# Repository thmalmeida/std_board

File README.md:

# std_board
_std_board_ is an open hardware project that aims to bring the connectivity capacity of a microcontroller joining with sensors and actuators to a remote monitoring and control.

Renderized PCB with electrical components and modules are showed on the following picture.

# update logs

- 20210901
  + Voltage divider resistor values has been calculated sucessfully;
  + AC voltage measure sensor simulation has updated for 127 and 220 Vrms;
  + 

- 20210719
 - Fix voltage measure circuit on R58;
 - Modify voltage measure input borne to left side board avoid AC DC short circuits

# Content

* [About std_board](#about-std_board)
* [Features](#features)
* [Peripherals mapping](#peripherals-mapping)
* [Digital inputs](#digitadigitall-inputs)
* [Level sensor](#level-sensor)
* [Voltage sensor](#voltage-sensor)
* [Power input modes](#power_input_modes)
  + [Mode 1: 120-240 VAC input](#mode-1-120-240-vac-input)
  + [Mode 2: 24 VAC input](#mode-2-24-vac-input)
  + [Mode 3: 5 Vdc (external power supply)](#mode-3-5V)
* [Current controller](#current-controller)
* [AC load drive](#ac-load-drive)
* [Erros fixed on v0.1.0](#erros)

## About std_board

The main idea of std_board is help farmers to optimize production and monitoring some variables. Even this hardware is a little bit generic pplication that can control water pumps, valves, solenoids and any AC load. For this, it needs some feedback o real world physical variables like water weel level, time, water pressure inside pumps, ac voltage, ac current, thermal relay, and any digital input. The general purpose is optimize the production controlling the water flux.

The main concept of this system is interfaces one processor, e.g. ESP32, with electrical AC loads and physical parameters.

## Peripherals mapping

Pin map table of ESP32 onboard connections
.

The onboard system has the following connectivities:

## Features
This board has few hardware printed circuits that interfaces the ESP32 with real world variables conditioning physical variables to low voltages signals readable for input micro controller.

* Digital I/O (four)
* Input for pressure sensor;
* Input for temperature one wire temperature sensor (e.g. DS18B20);
* Umidity sensor DHT11;
* Current controller using internal DAC and onboard circuit processing;
* Protection circuit;
* AC voltage sensor;
* AC current sensor;
* AC load drive;
* JTAG connector - for debbugger (e.g. FT2232H);
* I2C connection for RTC module (e.g. DS3231);
* I2C connection for barometric sensor (e.g. BMP280);
* Four independent water level sensor circuits;
* Onboard LED indicator;
* Power supply with capability with different voltage levels input;

### Digital I/O

Four digital I/O are mounted with 56 kOhms pull up resistors and low pass filter using 47 nF capactitor. The circuit are showing on the following Figure.

### Level sensor

This board has four independent water level sensor circuit. Each circuit uses one BJT (bipolar junction transistor) and has one jump to exclude this transistor if desired. The main concept of this circuit a voltage division with amplification. The transistor has the function to amplifier the signal and transform it in a digital.

Some simulation has been done

## Voltage sensor
The voltage sensor can measure four different source of voltages into one selected soldering jump. The following Figure shows the schematic of voltage sensor circuit.

## Power input modes

### Mode 1: 120-240 VAC input
This mode
to 12VDC and 120 mA;
### Mode 2: 24 VAC to 5 VDC;
20211012 - This mode should be defined, calculated e design in a future moment. Linear regulation has a big waste on drop difference voltage when the input is ~40 V. Bests solutions were found using switching regulators. LNK30x series has bigger input AC voltage. Some candidates with low voltages are:

- LM2576
- LM2596
- DPA422GN
- XL7015

Switches regulators has best efficiency when drop difference voltage are considerable.

### Mode 3: 5 Vdc (external power supply)

If the system is powered with external 5 V power supply on Pwr_in_1 (0V) and Pwr_in_2 (+5V), it needs to solder some following jumps:

- J31: to jump F3 fuse;
- J32: to jump L1 protection inductor;
- J33 and J43: to jump rectifer 1;
- J40: to jump L2 filter;
- J41: link node A with node B;
- J44: link node B to node C;
- J42: jump 5 V regulation because it's powered directly with external 5 V;
- J35: to link the 5 V with whole system;

## Current controller

## AC load drive

This boards has three circuits to drive AC voltage from source to the load using TRIAC and optocoupler components. Some filters to avoid unexpected shots are implemented on the power side. The Figure bellow shows the drive where one high logic digital signal from +3,3 V to +5 V can be applied on <em>K1_out</em> point and shotting the TRIAC. The <em>Power_AC_2</em> is the main phase that drives throug the TRIAC to de <em>Load1</em> node. This load must be connected to another phase or to neutro to make a close circuit.

It needs to put a F1 fuse or solder J36 jump.

# Setup #1 on 0.1.0 version (20210310):

This part guide to build one setup to common use. The nexts steps should be followed to connect jumps to link electrical parts.

- J9: connect the common pad wire to 3.3V on water level circuits;
- R73: can be short circuited
- J27: exclude the first pad and connect T1 input to fifth pad;
- J16: substitute abstract diode D4 protection;
- J25: solder jump to connect L3 water level using GPIO14;
- J26: solder jump to connect L2 water level using GPIO12;
- J19: connect umidity sensor on GPIO13;

- Current source drive circuit
Should solder J24 to use ADC read on GPIO26 into ADC2_9;

## Hardware mounted onboard

* Pressure circuit bias 1;
* Pressure circuit bias 2;

# Setup #2

# Setup #3

# Tips
To use L1 and L4 circuit level sensor should solder the following jumps:

L1: put jump J22 closed;
L4: put jump J7 closed;

# Errors

- Voltage sensor

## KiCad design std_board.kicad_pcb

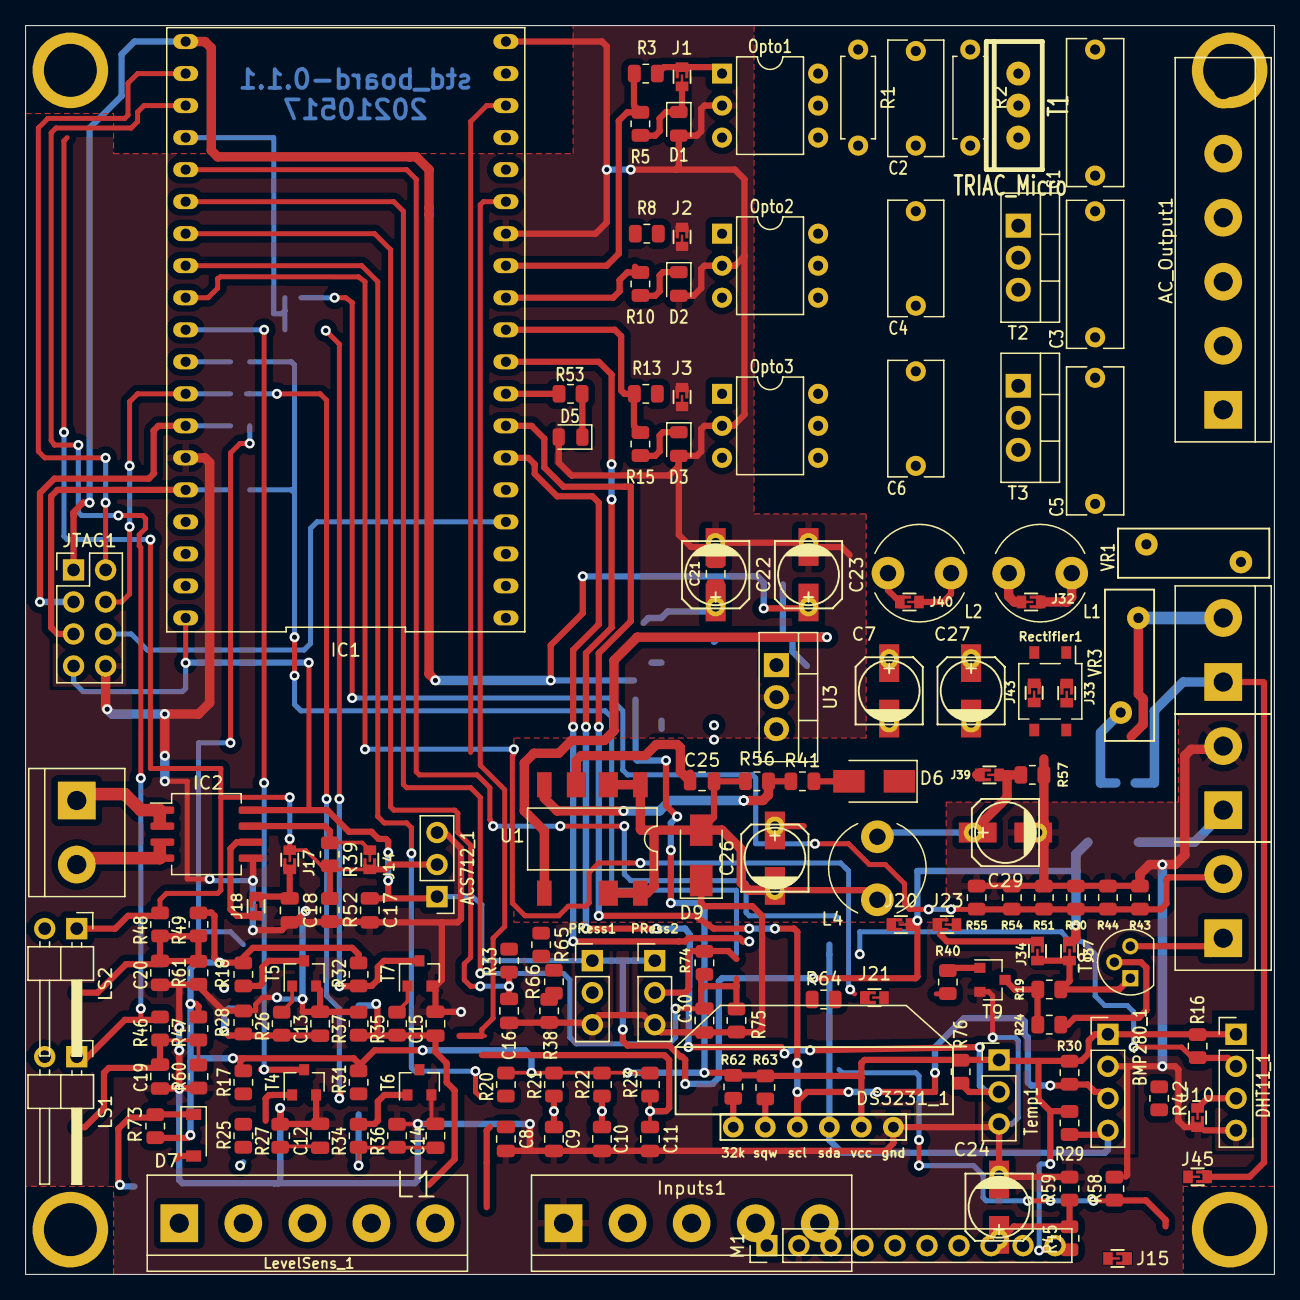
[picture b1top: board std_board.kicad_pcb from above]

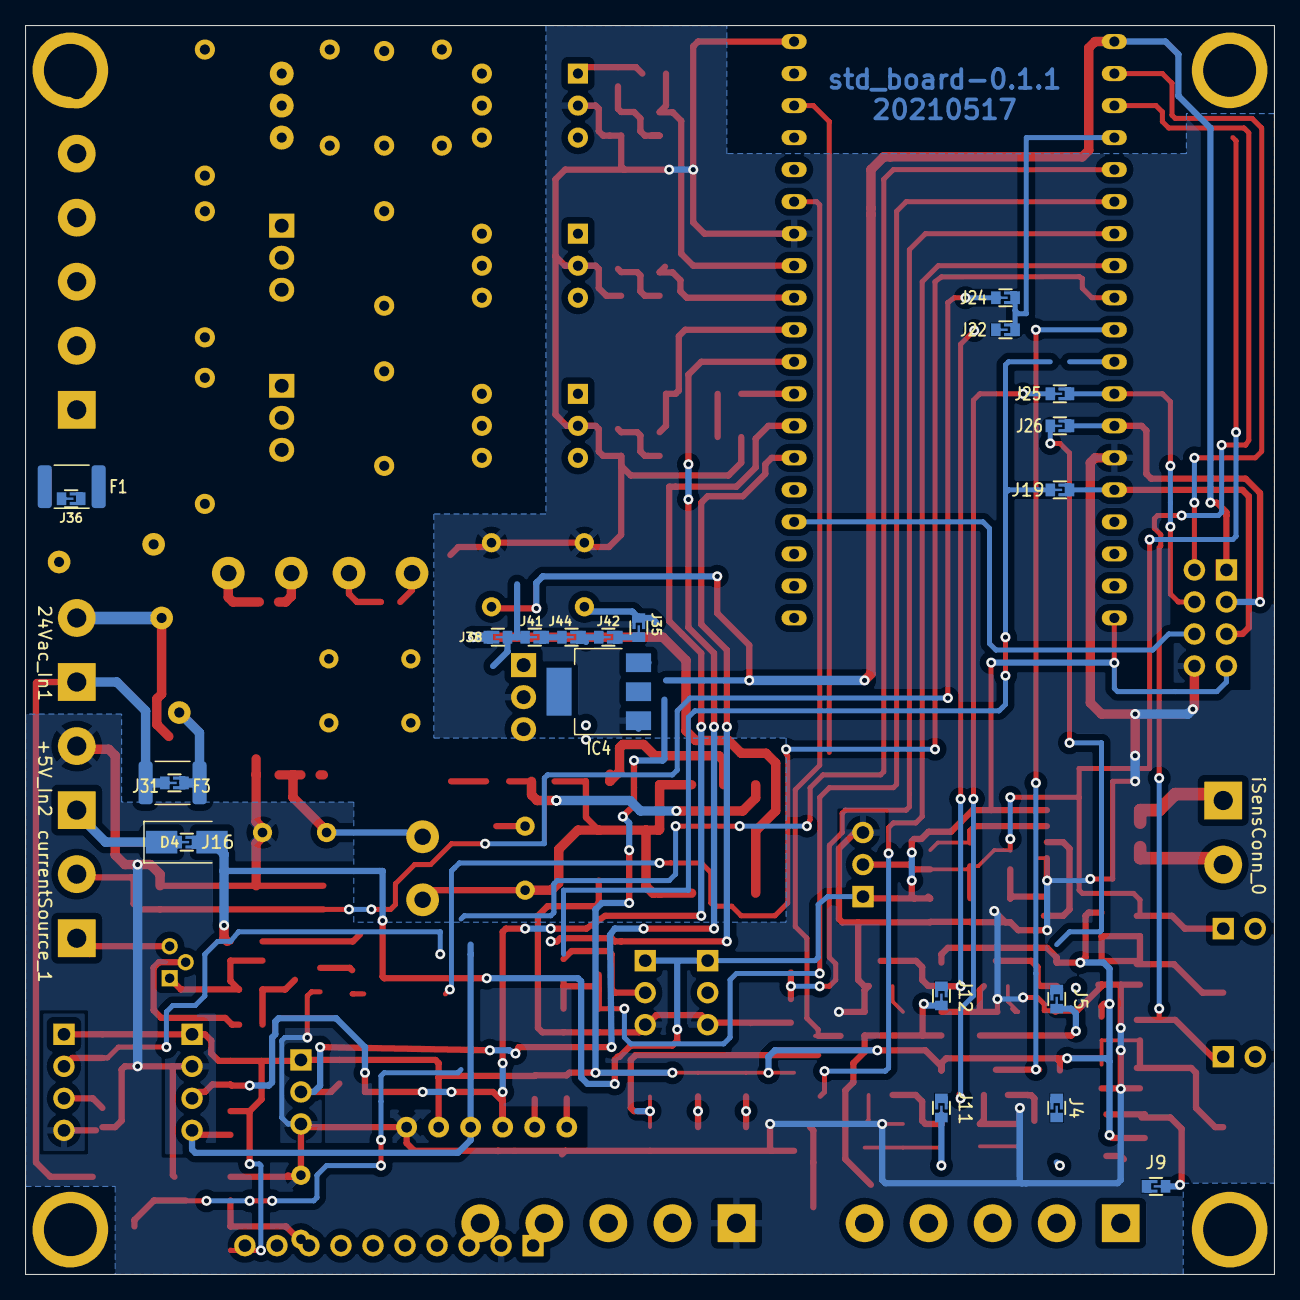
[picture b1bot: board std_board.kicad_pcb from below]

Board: 2 copper layers, 99.1 x 99.1 mm, 184 parts (22 on the bottom side), 87 nets.

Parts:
24Vac_In1: PowerSupply; TerminalBlock_bornier-2_P5.08mm
+5V_In2: +5V; TerminalBlock_bornier-2_P5.08mm
ACS712_1: ACS712_Module; PinHeader_1x03_P2.54mm_Vertical
AC_Output1: Driver_AC_1; TerminalBlock_bornier-6_P5.08mm
BMP280_1: BMP280; PinHeader_1x04_P2.54mm_Vertical
C1, C3, C5: 10 nF; C_Rect_L11.5mm_W4.3mm_P10.00mm_MKT
C2, C4, C6: 47 nF; C_Rect_L9.0mm_W4.2mm_P7.50mm_MKT
C7: 47 uF; C3_elec_5x4.5_pth
C8, C9, C10, C11: 47 nF; C_0805_2012Metric
C12, C13, C14, C15, C16, C30: 10 nF; C_0805_2012Metric
C17: 0.1 uF; C_0805_2012Metric
C18: 1 nF; C_0805_2012Metric
C19, C20, C21: 1 uF; C_0805_2012Metric
C22: 2.2 uF; C3_elec_5x4.5_pth
C23, C24: 22 uF; C3_elec_5x4.5_pth
C25: 100 nF; C_0805_2012Metric
C26: 10 uF; C3_elec_5x4.5_pth
C27: 4.7 uF; C3_elec_5x4.5_pth
C29: 100 uF; C3_elec_5x4.5_pth
D1, D2, D3, D5: Led_Micro; LED_0805_2012Metric
D4: Diode; D_SMA
D6: 1N4005GP; D_SMA
D7: Diode; D_SOD-123
D9: UF4005; D_SMA
DHT11_1: DHT11; PinHeader_1x04_P2.54mm_Vertical
DS3231_1: DS3231_1; DS3231_module_vertical
E1, E2, E3, E4: ScrewHole; ScrewHole_4.2mm
F1, F3: Fuse; Fuse_1812_4532Metric
IC1: ESP32; ESP32_DEVKIT
IC2: ACS712; SO-8_5.3x6.2mm_P1.27mm
IC4: AMS1117-V; SOT-223
Inputs1: CONN_5X1; TerminalBlock_bornier-5_P5.08mm
J1, J2, J3, J4, J5, J9, J11, J12, J14, J15, J17, J18, J19, J20, J21, J22, J23, J24, J25, J26, J31, J32, J33, J34, J35, J36, J37, J38, J39, J40, J41, J42, J43, J44, J45: Jumper; J_0603
J10: J_DHT11; J_0603
J16: J_PRess; J_0603
JTAG1: JTAG_CONN-06_adapted; PinHeader_2x04_P2.54mm_Vertical
L1, L2: L_Micro; L_Radial_D7.5mm_P5.00mm_Fastron_07P
L4: 1 mH; L_Radial_D7.5mm_P5.00mm_Fastron_07P
LS1, LS2: I_sens; PinHeader_1x02_P2.54mm_Horizontal
LevelSens_1: levelSensors; TerminalBlock_bornier-5_P5.08mm
M1: ADS1x15_module; PinHeader_1x10_P2.54mm_Vertical
Opto1, Opto2, Opto3: Optocoupler; DIP-6_W7.62mm
PRess1, PRess2: pressureSensor; PinHeader_1x03_P2.54mm_Vertical
R1: 330; R_Axial_DIN0207_L6.3mm_D2.5mm_P7.62mm_Horizontal
R2: 470; R_Axial_DIN0207_L6.3mm_D2.5mm_P7.62mm_Horizontal
R3, R8, R13: 680; R_0805_2012Metric
R5, R10, R15: 1 k; R_0805_2012Metric
R16, R76: 4.7 k; R_0805_2012Metric
R17, R18, R31, R32: 560 k; R_0805_2012Metric
R19: 47 k; R_0805_2012Metric
R20, R21, R22, R23, R47: 56 k; R_0805_2012Metric
R24, R39: 2.2 k; R_0805_2012Metric
R25, R26, R34, R35: 33 k; R_0805_2012Metric
R27, R28, R36, R37, R64: 220 k; R_0805_2012Metric
R29, R30: R_Micro; R_0805_2012Metric
R33, R74: 12 k; R_0805_2012Metric
R38, R65, R66, R75: 6.8 k; R_0805_2012Metric
R40: 100 k; R_0805_2012Metric
R41: 13 k; R_0805_2012Metric
R42: 1 M; R_0805_2012Metric
R43, R44, R50, R51, R54, R55: 30; R_0805_2012Metric
R45, R60: 39 k; R_0805_2012Metric
R46, R48, R52, R57, R58: 3.3 k; R_0805_2012Metric
R49: 180 k; R_0805_2012Metric
R53: 510; R_0805_2012Metric
R56: 2.05 k; R_0805_2012Metric
R59, R61: 120 k; R_0805_2012Metric
R62, R63: 10 k; R_0805_2012Metric
R73: 70 k; R_0805_2012Metric
Rectifier1: DF10S; TO-269AA
T1: TRIAC_Micro; TO-220_thm
T2, T3: TRIAC_Micro; TO-220-3_Vertical
T4, T5, T6, T7, T9: NPN_MMBT222A; SOT-23
T8: PNP_2N3906; TO-92
Temp1: DS18B20; PinHeader_1x03_P2.54mm_Vertical
U1: LNK306; PowerIntegrations_SMD-8B
U3: L7805CV; TO-220-3_Vertical
VR1, VR3: VR_Micro; RV_Disc_D12mm_W3.9mm_P7.5mm
currentSource_1: Connector_2; TerminalBlock_bornier-2_P5.08mm
iSensConn_0: sensConn; TerminalBlock_bornier-2_P5.08mm

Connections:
/1wire_Data: IC1.28 (U2_TXD/GPIO17), R76.1 (A), Temp1.2
/32K: DS3231_1.6, R62.2 (B)
/+3.3V: BMP280_1.1, C23.1, DHT11_1.1, DS3231_1.2, IC1.1 (3V3), IC4.2 (OUT), JTAG1.1 (VTref/3V3), R16.1 (A), R17.1 (A), R18.1 (A), R20.1 (A), R21.1 (A), R22.1 (A), R23.1 (A), R29.1 (A), R30.1 (A), R31.2 (B), R32.2 (B), R45.1 (A), R47.1 (A), R49.1 (A), R62.1 (A), R63.1 (A), R73.1 (A), R76.2 (B), Temp1.1
/+5V: ACS712_1.1, C17.1 (A), C21.1 (A), C22.1, D4.2 (-Cathode), IC1.19 (5V5), IC2.8, IC4.3 (IN), J16.1 (A), J35.1 (A), J37.1 (A), J42.1 (A), JTAG1.7 (+5V), M1.1, PRess1.1, PRess2.1, U3.1 (IN)
/A: C7.1, J38.2 (B), J40.1 (A), J41.2 (B), L2.1 (A)
/ADC_1: J24.2 (B), R43.2 (B), R44.2 (B), R50.2 (B), R51.2 (B), R54.2 (B), R55.2 (B), currentSource_1.2 (S2)
/B: J41.1 (A), J44.2 (B)
/C: J34.1 (A), J39.1 (A), J42.2 (B), J44.1 (A), U3.3 (OUT)
/Common: AC_Output1.5, J23.2 (B), R64.1 (A), VR1.2
/DAC_1: IC1.9 (GPIO25/ADC2_8/DAC_1), R40.1 (A)
/DHT11_data: DHT11_1.2, J19.2 (B), R16.2 (B)
/Debug_RX: IC1.27 (U2_RXD/GPIO16), R53.1 (A)
/IP+: IC2.1, IC2.2, iSensConn_0.1 (S1)
/IP-: IC2.3, IC2.4, iSensConn_0.2 (S2)
/K1_in: C8.1 (A), IC1.37 (SPI_MOSI/GPIO23), Inputs1.2, R20.2 (B)
/K1_out: IC1.31 (SPI_MISO/GPIO19_(33)), R3.1 (A), R5.1 (A)
/K2_in: C9.1 (A), IC1.36 (U0_RTS/WIRE-SDL/GPIO22), Inputs1.3, R21.2 (B)
/K2_out: IC1.30 (SPI_SCK/GPIO18_(32)), R8.2 (B), R10.1 (A)
/K3_in: C10.1 (A), IC1.33 (Wire_SDA/GPIO21_(35)), Inputs1.4, R22.2 (B)
/K3_out: IC1.29 (SPI_SS/GPIO05), R13.1 (A), R15.1 (A)
/L1_in: IC1.10 (GPIO26/ADC2_9/DAC_2), J4.1 (A), R17.2 (B), T4.3
/L1_probe: C12.1 (A), J4.2 (B), LevelSens_1.2, R25.1 (A), R27.1 (A)
/L2_in: IC1.11 (GPIO27/ADC2_7), J5.1 (A), R18.2 (B), T5.3
/L2_probe: C13.1 (A), J5.2 (B), LevelSens_1.3, R26.1 (A), R28.1 (A)
/L3_in: J11.1 (A), J25.2 (B), R31.1 (A), T6.3
/L3_probe: C14.1 (A), J11.2 (B), LevelSens_1.4, R34.1 (A), R36.1 (A)
/L4_in: J12.1 (A), J26.2 (B), R32.1 (A), T7.3
/L4_probe: C15.1 (A), J12.2 (B), LevelSens_1.5, R35.1 (A), R37.1 (A)
/Load01: AC_Output1.1, C1.2 (B), C2.2 (B), J20.1 (A), T1.1 (K)
/Load02: AC_Output1.2, C3.2 (B), C4.2 (B), T2.1
/Load03: AC_Output1.3, C5.2 (B), C6.2 (B), T3.1
/NRST: IC1.2 (RST/JTAG_RST/CHIP-PU), JTAG1.2 (nTRST)
/PRess_1: C16.1 (A), IC1.6 (GPIO35/ADC1_7), R33.2 (B), R38.1 (A), R65.1 (A)
/PRess_2: C30.1 (A), IC1.7 (GPIO32/ADC1_4), R66.1 (A), R74.2 (B), R75.1 (A)
/Power_AC_2: F1.1, T2.2, T3.2, VR1.1
/Power_AC_R: J36.2 (B), R2.1 (A), T1.2 (A)
/Power_AC_R_2: J15.1 (A), J36.1 (A)
/SCL: BMP280_1.3, DS3231_1.4, IC1.26 (ADC2_0/GPIO04), M1.3, R30.2 (B)
/SDA: BMP280_1.4, DS3231_1.3, IC1.25 (ADC2_1/GPIO00), M1.4, R29.2 (B)
/SQW: DS3231_1.5, R63.2 (B)
/T1_in: C11.1 (A), IC1.8 (GPIO33/ADC1_5/TOUCH8/XTAL32), Inputs1.5, R23.2 (B)
/TDO: IC1.23 (TDO/ADC2_3/GPIO15), JTAG1.6 (TDO)
/V_external: AC_Output1.6, J21.1 (A)
/V_input: 24Vac_In1.1 (S1), F3.2, J31.2 (B), J45.1 (A)
/iSensor1: IC1.3 (GPIO36/ADC1_0/SensVP/ADC_PA/RTCIO_0), LS1.1 (A), R46.1 (A)
/iSensor2: ACS712_1.2, J14.1 (A), J17.2 (B), J22.2 (B), LS2.1 (A), R39.2 (B), R48.1 (A), R52.1 (A)
/vSensorR: IC1.5 (GPIO34/ADC1_6/VDET-1/RTCIO4), R42.2 (B), R58.1 (A)
GND: +5V_In2.2 (S2), ACS712_1.3, BMP280_1.2, C7.2 (GND), C8.2 (B), C9.2 (B), C10.2 (B), C11.2 (B), C12.2 (B), C13.2 (B), C14.2 (B), C15.2 (B), C16.2 (B), C17.2 (B), C18.2 (B), C19.2 (B), C20.2 (B), C21.2 (B), C22.2 (GND), C23.2 (GND), C24.2 (GND), C27.2 (GND), C29.2 (GND), C30.2 (B), D1.2, D2.2, D3.2, D5.2, D9.1 (+Anode), DHT11_1.4, DS3231_1.1, IC1.14 (GND), IC1.32 (GND_(34)), IC1.38 (GND), IC2.5, IC4.1 (GND), Inputs1.1, J10.1 (A), J43.1 (A), JTAG1.8 (GND), M1.2, Opto1.2, Opto2.2, Opto3.2, PRess1.3, PRess2.3, R27.2 (B), R28.2 (B), R36.2 (B), R37.2 (B), R38.2 (B), R43.1 (A), R44.1 (A), R50.1 (A), R51.1 (A), R52.2 (B), R54.1 (A), R55.1 (A), R57.2 (B), R59.2 (B), R60.2 (B), R61.2 (B), R65.2 (B), R66.2 (B), R75.2 (B), Rectifier1.2 (Negative), T4.2, T5.2, T6.2, T7.2, T9.2, Temp1.3, U3.2 (GND)
unnamed: 24Vac_In1.2 (S2), J43.2 (B), Rectifier1.3 (AC_Input)
unnamed: +5V_In2.1 (S1), D4.1 (+Anode), J16.2 (B)
unnamed: C2.1 (A), R1.2 (B), R2.2 (B)
unnamed: C18.1 (A), J17.1 (A), J18.1 (A)
unnamed: C19.1 (A), LS1.2 (B), R46.2 (B), R47.2 (B), R60.1 (A)
unnamed: C20.1 (A), LS2.2 (B), R48.2 (B), R49.2 (B), R61.1 (A)
unnamed: C25.1 (A), U1.3 (BP)
unnamed: C25.2 (B), C26.2 (GND), D9.2 (-Cathode), L4.1 (A), R56.2 (B), U1.1 (S), U1.2 (S), U1.7 (S), U1.8 (S)
unnamed: J1.2 (B), R5.2 (B)
unnamed: J2.2 (B), R10.2 (B)
unnamed: J3.2 (B), R15.2 (B)
unnamed: C29.1, D6.1 (+Anode), J39.2 (B), L4.2 (B), R57.1 (A)
unnamed: C26.1, D6.2 (-Cathode), R41.2 (B)
unnamed: D7.1 (+Anode), J9.2 (B), R73.2 (B)
unnamed: D7.2 (-Cathode), J9.1 (A), LevelSens_1.1
unnamed: J31.1 (A), J32.2 (B), L1.2 (B)
unnamed: F3.1, VR3.1
unnamed: J14.2 (B), R39.1 (A)
unnamed: J1.1 (A), R3.2 (B)
unnamed: J2.1 (A), R8.1 (A)
unnamed: J3.1 (A), R13.2 (B)
unnamed: J15.2 (B), J20.2 (B), J21.2 (B), J45.2 (B), R42.1 (A)
unnamed: C24.1, J23.1 (A), R45.2 (B), R58.2 (B), R59.1 (A), R64.2 (B)
unnamed: J32.1 (A), J33.2 (B), L1.1 (A), Rectifier1.4 (AC_Input)
unnamed: C27.1, J33.1 (A), J40.2 (B), L2.2 (B), Rectifier1.1 (Positive)
unnamed: J34.2 (B), J37.2 (B), R19.2 (B), T8.1 (E)
unnamed: J38.1 (A), U1.5 (D)
unnamed: Opto2.4, T2.3
unnamed: Opto3.4, T3.3
unnamed: R19.1 (A), R24.2 (B)
unnamed: R24.1 (A), T8.2 (B)
unnamed: PRess1.2, R33.1 (A)
unnamed: R41.1 (A), R56.1 (A), U1.4 (FB)
unnamed: PRess2.2, R74.1 (A)
unnamed: T8.3 (C), currentSource_1.1 (S1)
P03: IC1.4 (GPIO39/ADC1_3/SensVN/RTCIO-3/ADC-PA), J22.1 (A), J24.1 (A)
P12: IC1.12 (GPIO14/ADC2_6/TMS), J25.1 (A), JTAG1.4 (TMS)
P13: IC1.13 (GPIO12/ADC2_5/TDI), J26.1 (A), JTAG1.3 (TDI)
P15: IC1.15 (GPIO13/ADC2_4/TCK), J19.1 (A), JTAG1.5 (TCK)

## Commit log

2021-03-10 started!
2021-03-10 new line added
2021-03-10 gerber updated on 20210310-2044
2021-03-11 Gerber files added
2021-05-28 updates on circuit board and readme file
2021-05-28 AC load explanation
2021-05-28 pin map Figure updated
2021-07-19 TODO list added on REAME.md
2021-07-19 voltage sensor new structure part 1
2021-09-02 voltage sensor: calculated resistors
2021-09-11 fixed voltage divider of pressure circuit design
2021-09-17 recalculated ADC voltage divider measurement
2021-09-22 updated board image with pinmap description
2021-09-22 updated pin map table
2021-09-24 recalculated current sensor resistors and changed pins and jumps of levels and sensors
2022-11-03 added new triac circuit upgrade to soft starter
2023-08-31 board update some documentation of pinout link with description
2023-12-27 current sensor 1 added resistors for voltage divider
2024-02-16 changed pi filter values at input of power supply
2024-02-16 moved backups to another place
